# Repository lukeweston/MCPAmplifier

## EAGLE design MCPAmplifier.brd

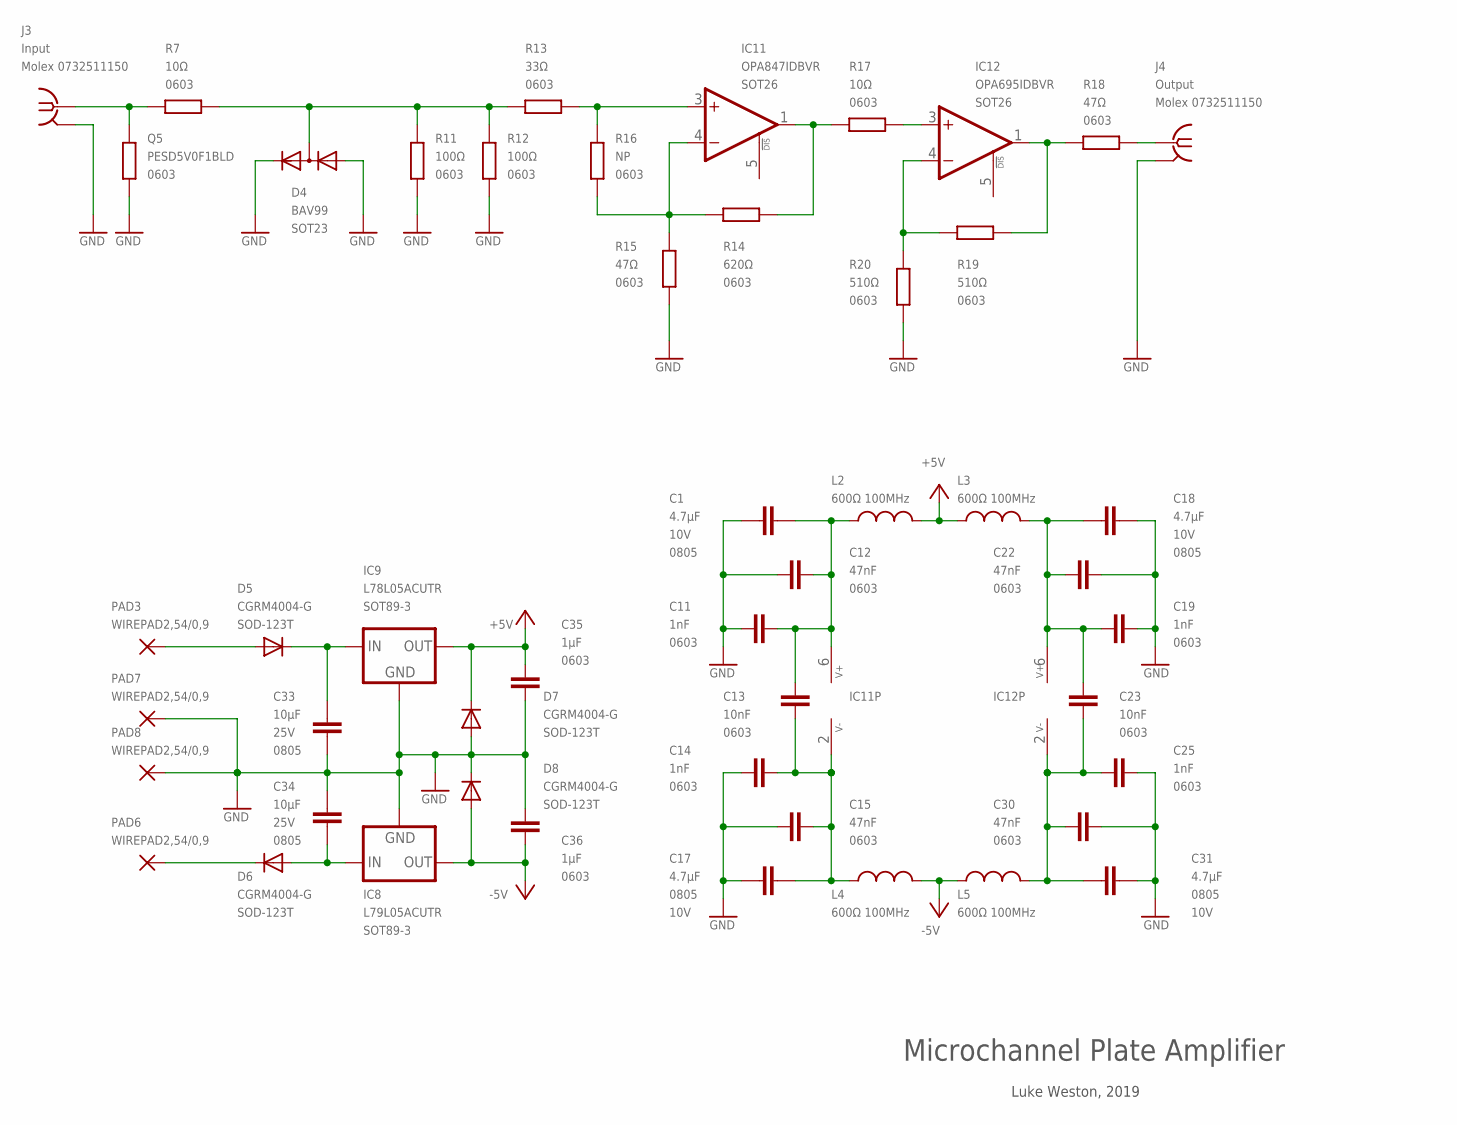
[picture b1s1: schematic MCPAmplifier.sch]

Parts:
C1, C17, C18, C31: 4.7µF; 0805; VOLTAGE 10V
C11, C14, C19, C25: 1nF; 0603
C12, C15, C22, C30: 47nF; 0603
C13, C23: 10nF; 0603
C33, C34: 10µF; 0805; VOLTAGE 25V
C35, C36: 1µF; 0603
D4: BAV99; SOT23
D5, D6, D7, D8: CGRM4004-G; SOD-123_MINI-SMA
IC8: L79L05ACUTR; SOT89
IC9: L78L05ACUTR; SOT89
IC11: OPA847IDBVR; SOT23-6
IC12: OPA695IDBVR; SOT23-6
J3: Input; J502-ND-142-0701-881/886
J4: Output; J502-ND-142-0701-881/886
L2, L3, L4, L5: 600Ω 100MHz; 0603
PAD3, PAD6, PAD7, PAD8: WIREPAD2,54/0,9; 2,54/0,9
Q5: PESD5V0F1BLD; 0603
R7, R17: 10Ω; 0603
R11, R12: 100Ω; 0603
R13: 33Ω; 0603
R14: 620Ω; 0603
R15, R18: 47Ω; 0603
R16: NP; 0603
R19, R20: 510Ω; 0603

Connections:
+5V: C35.1, D7.C, IC9.1 (OUT), L2.2, L3.1
-5V: C36.2, D8.A, IC8.3 (OUT), L4.2, L5.1
GND: C1.2, C11.2, C12.2, C14.2, C15.2, C17.2, C18.2, C19.2, C22.2, C25.2, C30.2, C31.2, C33.1, C34.2, C35.2, C36.1, D4.1 (A), D4.2 (C), D7.A, D8.C, IC8.1 (GND), IC9.2 (GND), J3.G@1 (2), J3.G@2 (2), J3.G@3 (2), J3.G@4 (2), J4.G@1 (2), J4.G@2 (2), J4.G@3 (2), J4.G@4 (2), PAD7.1, PAD8.1, Q5.1, R11.1, R12.1, R15.2, R20.2
unnamed: C13.2, C14.1, C15.1, C17.1, IC11.2 (V-), L4.1
unnamed: D4.3 (AC), R7.2, R11.2, R12.2, R13.2
unnamed: J3.1, Q5.2, R7.1
unnamed: IC11.3 (+IN), R13.1, R16.1
unnamed: IC11.4 (-IN), R14.2, R15.1, R16.2
unnamed: IC11.1 (OUT), R14.1, R17.2
unnamed: IC12.3 (+IN), R17.1
unnamed: IC12.4 (-IN), R19.2, R20.1
unnamed: IC12.1 (OUT), R18.2, R19.1
unnamed: J4.1, R18.1
unnamed: C1.1, C11.1, C12.1, C13.1, IC11.6 (V+), L2.1
unnamed: C18.1, C19.1, C22.1, C23.1, IC12.6 (V+), L3.2
unnamed: C23.2, C25.1, C30.1, C31.1, IC12.2 (V-), L5.2
unnamed: D5.A, PAD3.1
unnamed: C33.2, D5.C, IC9.3 (IN)
unnamed: D6.C, PAD6.1
unnamed: C34.1, D6.A, IC8.2 (IN)

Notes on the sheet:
Microchannel Plate Amplifier
Luke Weston, 2019

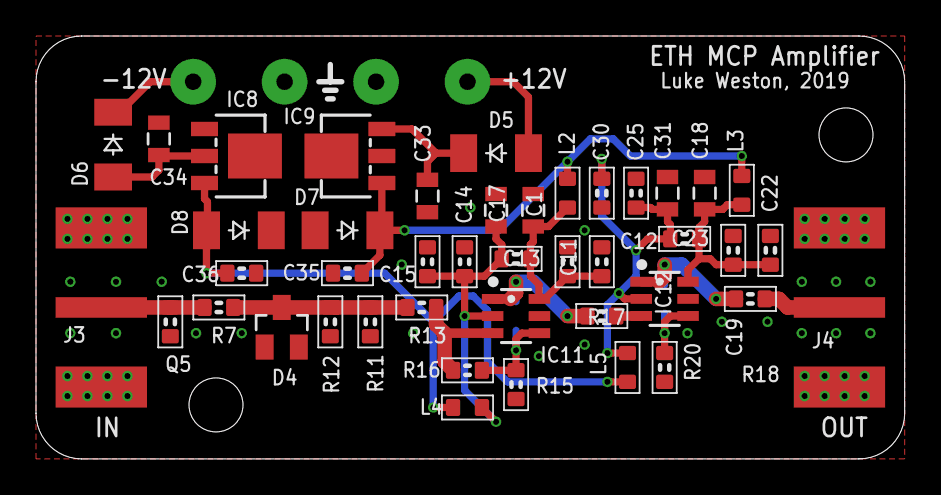
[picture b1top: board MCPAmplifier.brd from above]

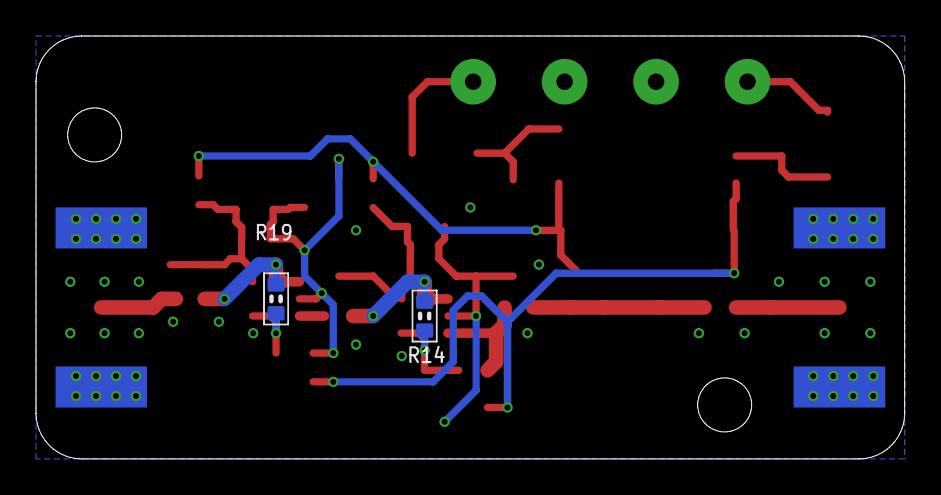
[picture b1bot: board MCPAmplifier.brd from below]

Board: 2 copper layers, 48.3 x 23.5 mm, 49 parts (2 on the bottom side), 20 nets.

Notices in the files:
parts and their libraries:
op-amp: Copyright (C) 2015, Bob Starr
